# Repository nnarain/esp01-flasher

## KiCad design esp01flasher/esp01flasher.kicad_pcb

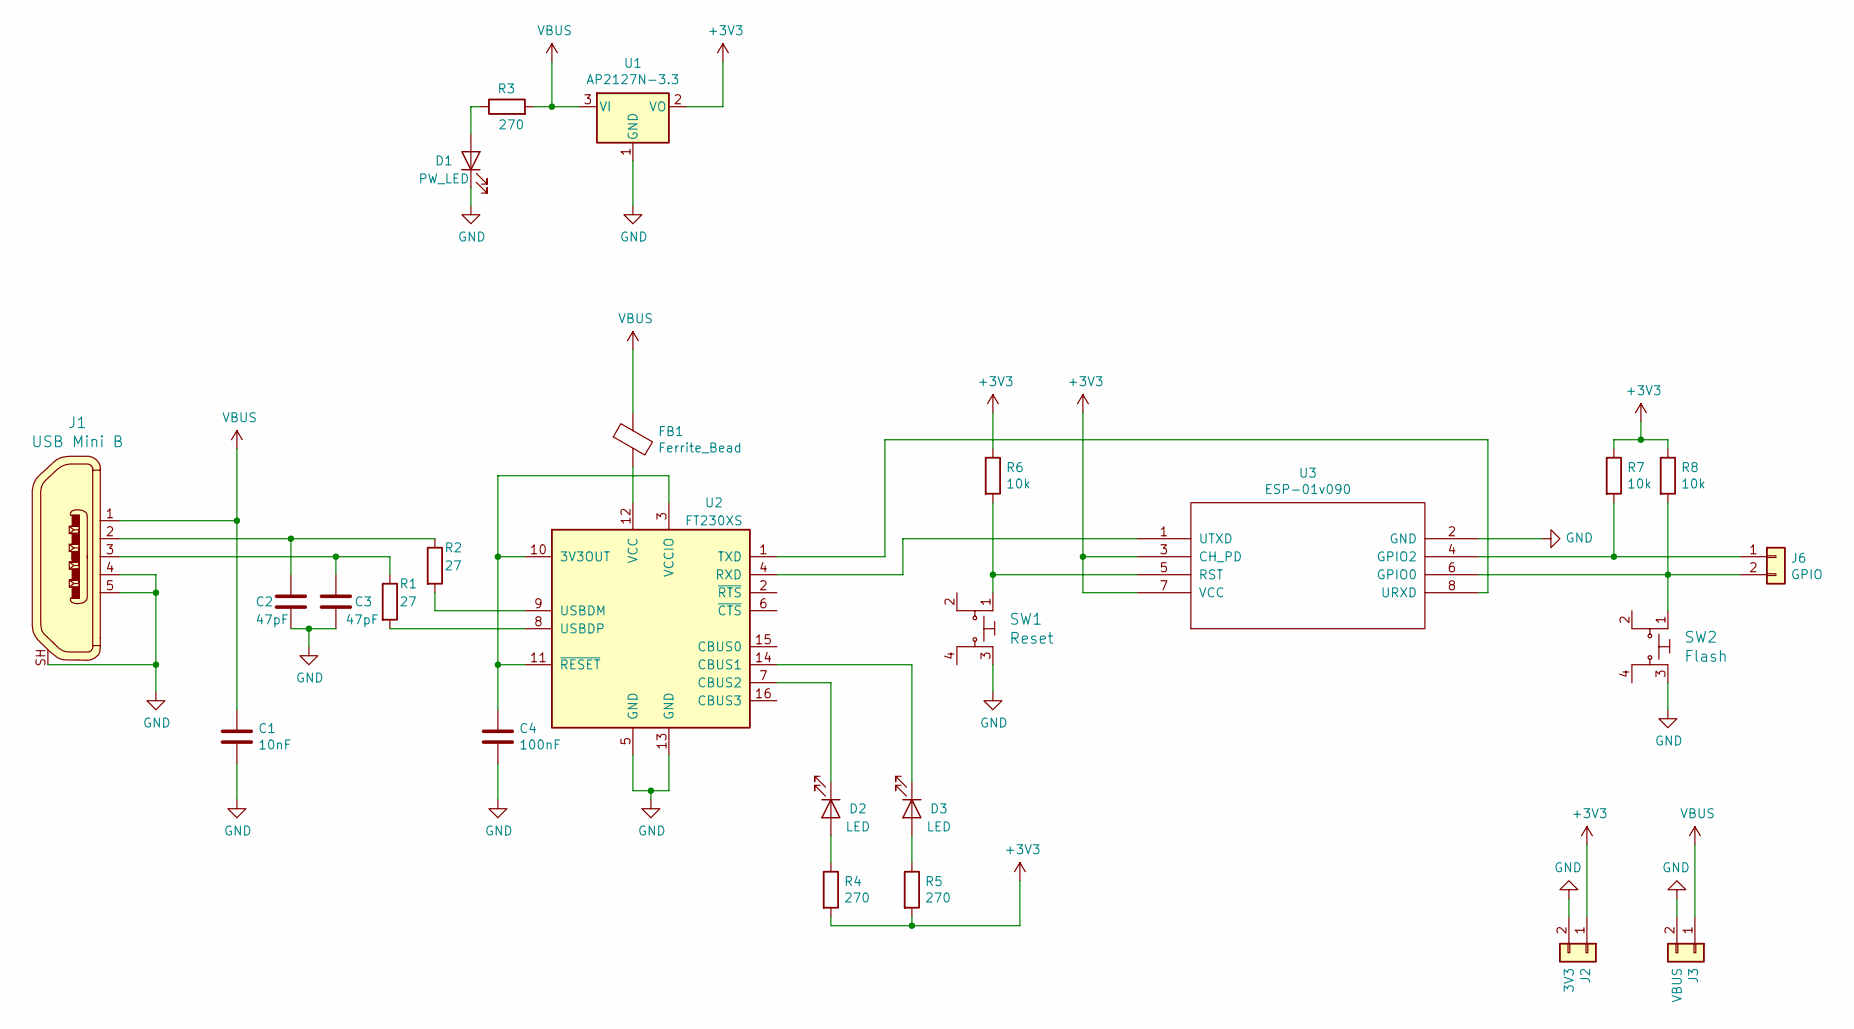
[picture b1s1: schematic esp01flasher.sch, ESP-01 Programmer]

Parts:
C1: 10nF; C_0201_0603Metric
C2, C3: 47pF; C_0201_0603Metric
C4: 100nF; C_0201_0603Metric
D1: PW_LED; LED_0402_1005Metric; Part Num VLMS1500-GS08TR-ND
D2, D3: LED; LED_0402_1005Metric
FB1: Ferrite_Bead; R_0603_1608Metric
J1: USB Mini B; USB_Micro_B_Female_10118192; MPN 10118192-0001LF; Digi-Key_PN 609-4613-1-ND
J2: 3V3; PinHeader_1x02_P2.54mm_Vertical
J3: VBUS; PinHeader_1x02_P2.54mm_Vertical
J6: GPIO; PinHeader_1x02_P2.54mm_Vertical
R1, R2: 27; R_0201_0603Metric
R3, R4, R5: 270; R_0201_0603Metric; Part Num YAG2337TR-ND
R6, R7, R8: 10k; R_0201_0603Metric
SW1: Reset; B3FS-1012P; MPN B3FS-1012P; Digi-Key_PN SW1237TR-ND
SW2: Flash; B3FS-1012P; MPN B3FS-1012P; Digi-Key_PN SW1237TR-ND
U1: AP2127N-3.3; SOT-23
U2: FT230XS; SSOP-16_3.9x4.9mm_P0.635mm
U3: ESP-01v090; ESP-01

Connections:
+3V3: J2.1, R4.2, R5.2, R6.1, R7.1, R8.1, U1.2 (VO), U3.3 (CH_PD), U3.7 (VCC)
GND: C1.2, C2.2, C3.2, C4.2, D1.1 (K), J1.4, J1.5, J1.SH, J2.2, J3.2, SW1.3, SW2.3, U1.1 (GND), U2.5 (GND), U2.13 (GND), U3.2 (GND)
unnamed: C2.1, J1.2, R2.1
unnamed: C3.1, J1.3, R1.1
unnamed: C4.1, U2.3 (VCCIO), U2.10 (3V3OUT), U2.11 (~RESET)
unnamed: D1.2 (A), R3.1
unnamed: D2.1 (K), U2.7 (CBUS2)
unnamed: D2.2 (A), R4.1
unnamed: D3.1 (K), U2.14 (CBUS1)
unnamed: D3.2 (A), R5.1
unnamed: FB1.2, U2.12 (VCC)
unnamed: J6.1, R7.2, U3.4 (GPIO2)
unnamed: J6.2, R8.2, SW2.1, U3.6 (GPIO0)
unnamed: R1.2, U2.8 (USBDP)
unnamed: R2.2, U2.9 (USBDM)
unnamed: R6.2, SW1.1, U3.5 (RST)
unnamed: U2.1 (TXD), U3.8 (URXD)
unnamed: U2.4 (RXD), U3.1 (UTXD)
VBUS: C1.1, FB1.1, J1.1, J3.1, R3.2, U1.3 (VI)

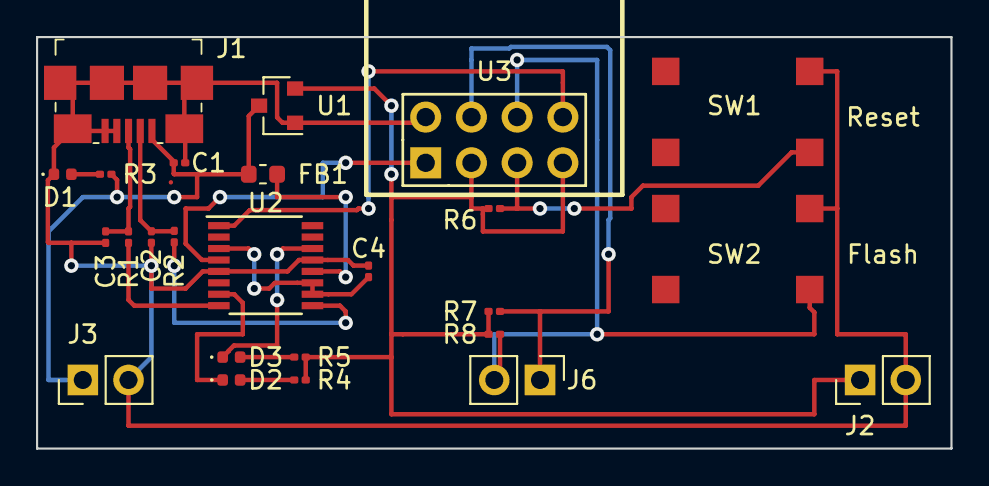
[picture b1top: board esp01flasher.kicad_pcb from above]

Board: 2 copper layers, 50.8 x 22.9 mm, 25 parts (0 on the bottom side), 19 nets.

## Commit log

2019-10-29 Schematic
2019-11-05 PCB Layout
2019-11-06 Added kicad-inventory as a submodule
